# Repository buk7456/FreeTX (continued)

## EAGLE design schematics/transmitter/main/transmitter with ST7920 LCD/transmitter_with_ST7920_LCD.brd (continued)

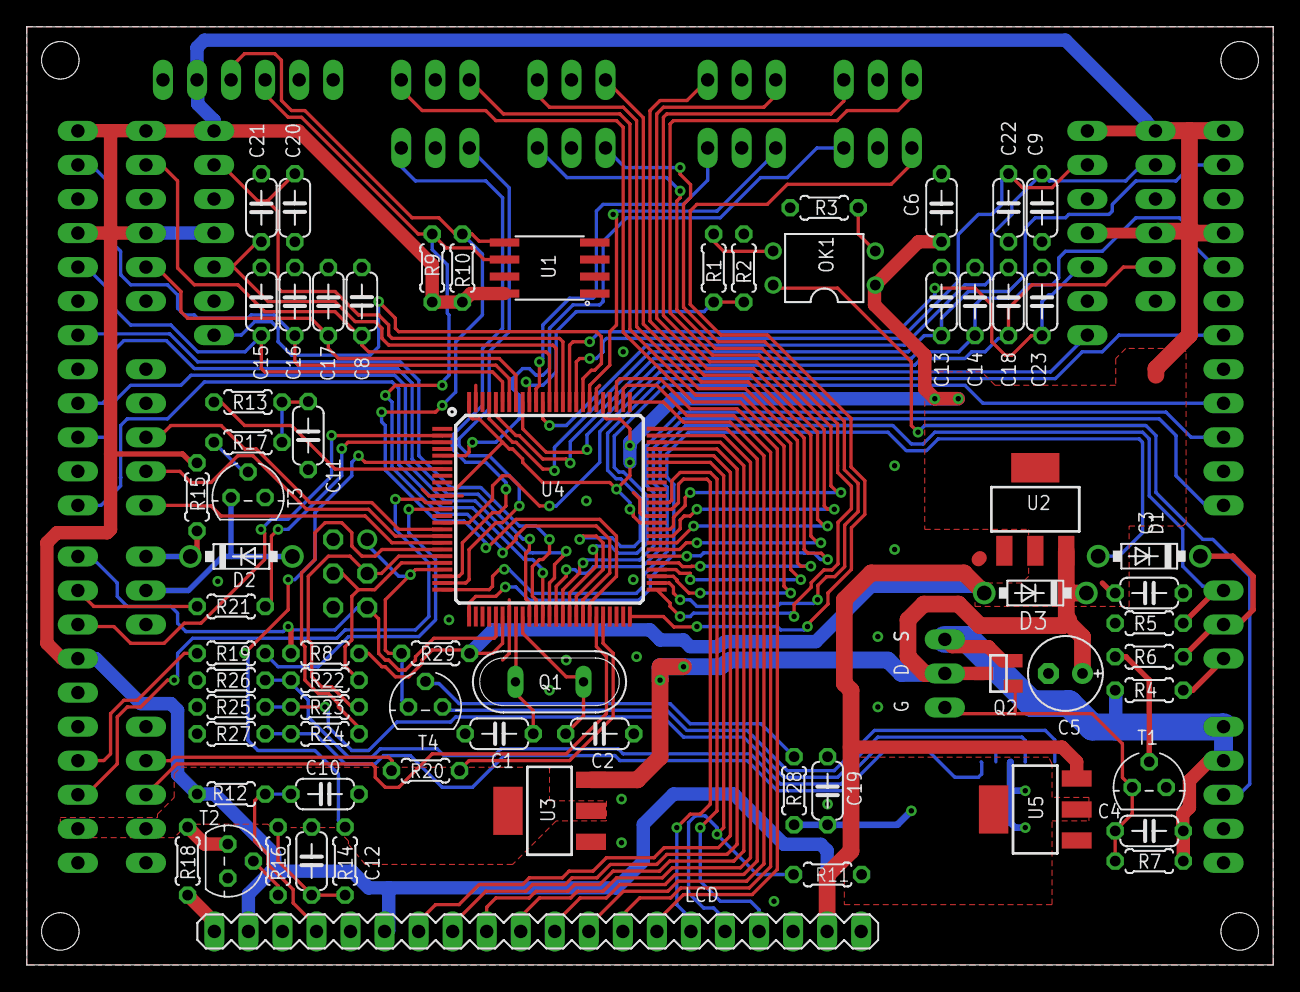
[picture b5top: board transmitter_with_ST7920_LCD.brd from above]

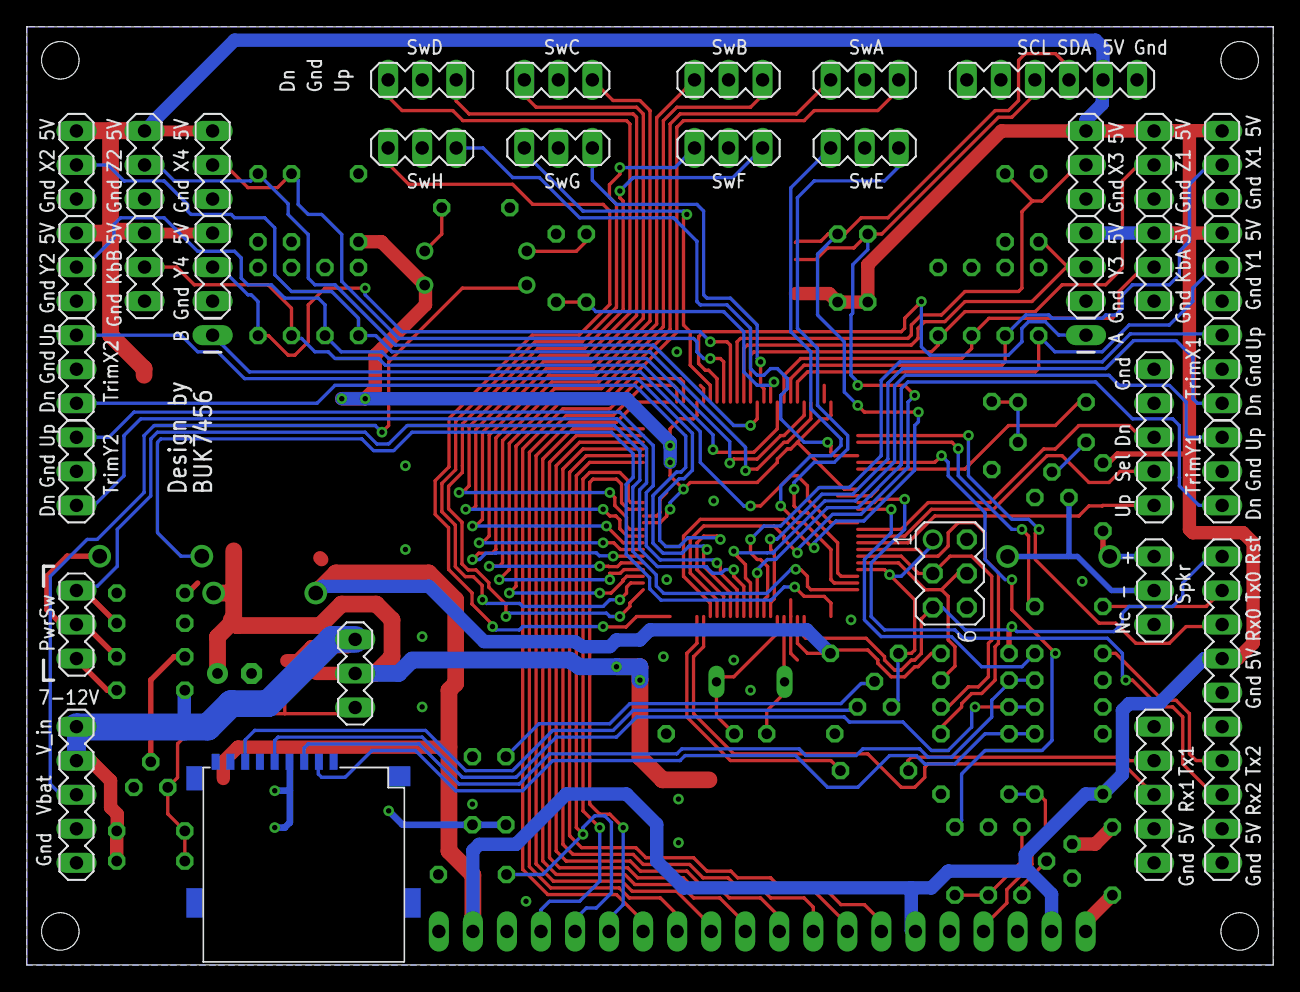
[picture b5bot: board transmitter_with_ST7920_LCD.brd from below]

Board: 2 copper layers, 93.0 x 70.0 mm, 104 parts (37 on the bottom side), 102 nets.

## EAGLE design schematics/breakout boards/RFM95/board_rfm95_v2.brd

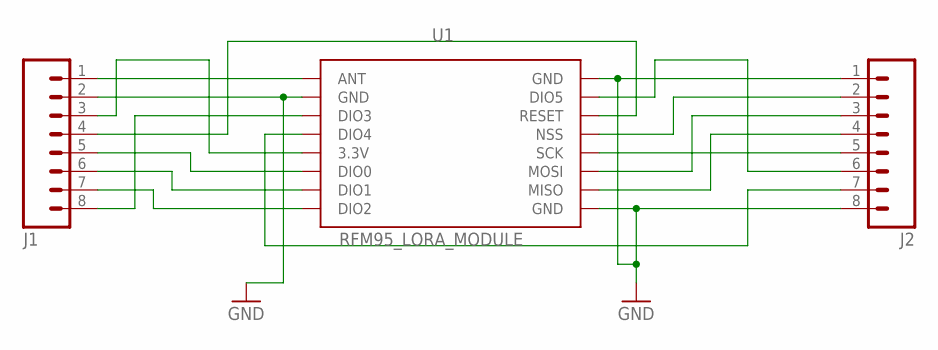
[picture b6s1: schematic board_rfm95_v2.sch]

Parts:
J1, J2: M08; 1X08_ROUND
U1: RFM95_LORA_MODULE; RFM95

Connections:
3.3V: J1.3, U1.3.3V
ANT: J1.1, U1.ANT
DIO0: J1.5, U1.DIO0
DIO1: J1.6, U1.DIO1
DIO2: J1.7, U1.DIO2
DIO4: J2.7, U1.DIO4
DIO5: J2.6, U1.DIO5
GND: J1.2, J2.1, J2.8, U1.GND, U1.GND@1 (GND), U1.GND@2 (GND)
MISO: J2.4, U1.MISO
MOSI: J2.3, U1.MOSI
unnamed: J1.8, U1.DIO3
NSS: J2.2, U1.NSS
RST: J1.4, U1.RESET
SCK: J2.5, U1.SCK

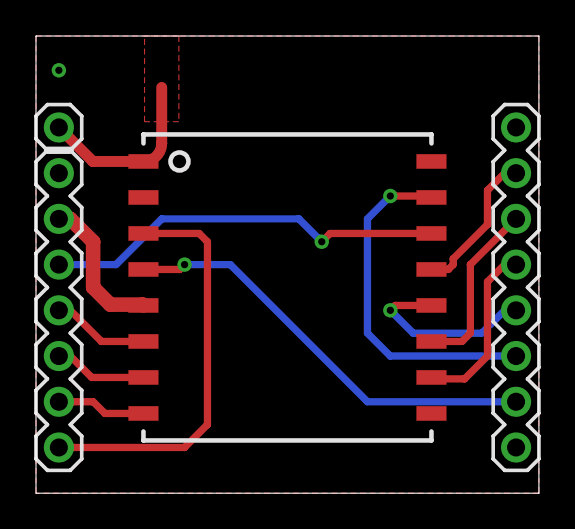
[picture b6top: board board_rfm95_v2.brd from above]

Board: 2 copper layers, 27.9 x 25.4 mm, 3 parts (0 on the bottom side), 14 nets.

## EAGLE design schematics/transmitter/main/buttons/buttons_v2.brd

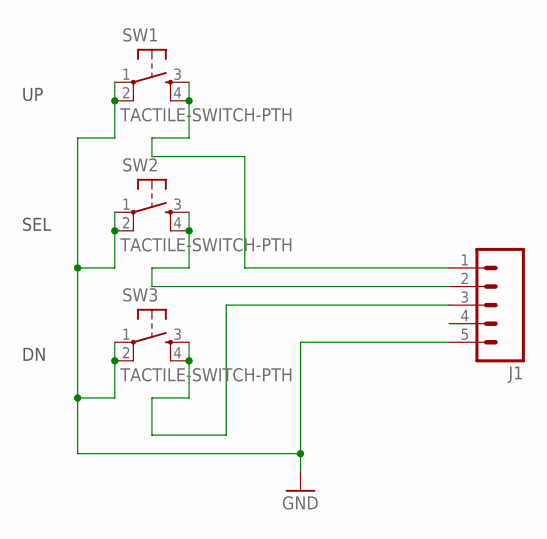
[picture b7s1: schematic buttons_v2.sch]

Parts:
J1: M05PTH; 1X05
SW1, SW2, SW3: TACTILE-SWITCH-PTH; TAC-SWITCH-PTH

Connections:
GND: J1.5, SW1.1, SW1.2, SW2.1, SW2.2, SW3.1, SW3.2
unnamed: J1.1, SW1.3, SW1.4
unnamed: J1.3, SW3.3, SW3.4
unnamed: J1.2, SW2.3, SW2.4

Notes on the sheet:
SEL

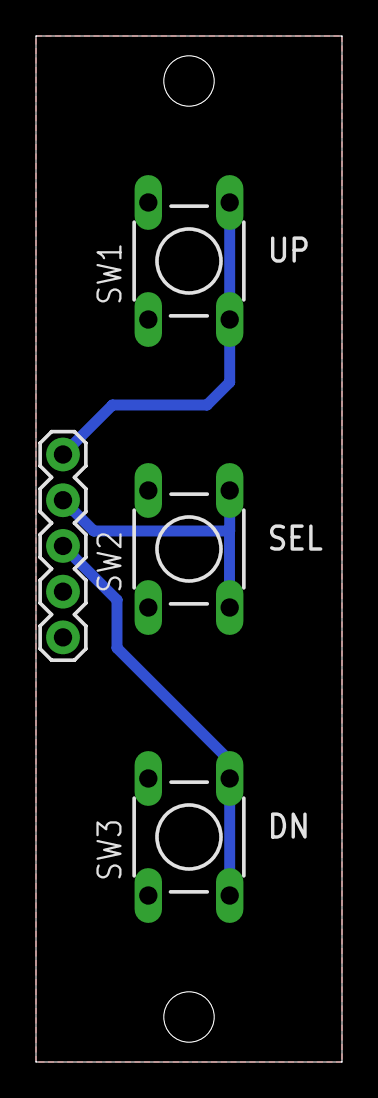
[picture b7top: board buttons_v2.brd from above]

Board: 2 copper layers, 17.0 x 57.0 mm, 4 parts (0 on the bottom side), 4 nets.

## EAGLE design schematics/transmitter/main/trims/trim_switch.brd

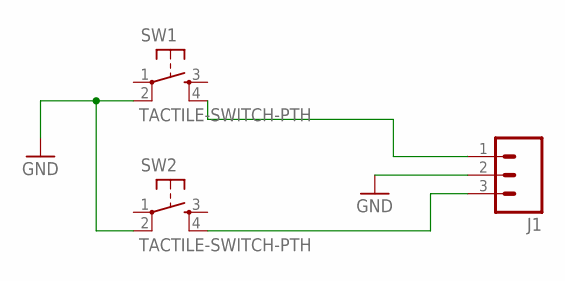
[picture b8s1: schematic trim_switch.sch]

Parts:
J1: M03PTH; 1X03
SW1, SW2: TACTILE-SWITCH-PTH; TAC-SWITCH-PTH

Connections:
GND: J1.2, SW1.2, SW2.2
unnamed: J1.1, SW1.4
unnamed: J1.3, SW2.4

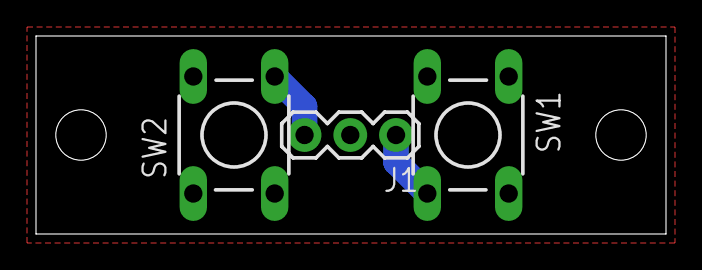
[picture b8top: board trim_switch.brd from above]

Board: 2 copper layers, 35.0 x 11.0 mm, 3 parts (0 on the bottom side), 3 nets.

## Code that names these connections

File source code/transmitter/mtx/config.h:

/*
 * config.h
 *
 * Basic settings such as:
 * - LCD controller
 * - UI to use
 * - Pin mapping
 * - External EEPROM 
 *
 */

#ifndef _CONFIG_H_
#define _CONFIG_H_

#define _FIRMWARE_VERSION "1.5.0"

//===========================================================================
//============================= LCD and UI ==================================
//===========================================================================

#define UI_128X64
// #define UI_84X48  //not implemented

#define DISPLAY_KS0108
// #define DISPLAY_ST7920
// #define DISPLAY_PCD8544 //not implemented

//===========================================================================
//============================= Pins and ports ==============================
//===========================================================================

//Name                 Arduino Pin

#define PIN_X1_AXIS      A3
#define PIN_Y1_AXIS      A2
#define PIN_X2_AXIS      A0
#define PIN_Y2_AXIS      A1
#define PIN_X3_AXIS      A11
#define PIN_Y3_AXIS      A10
#define PIN_X4_AXIS      A13
#define PIN_Y4_AXIS      A12

#define PIN_Z1_AXIS      A9
#define PIN_Z2_AXIS      A8

#define PIN_KNOB_A       A4
#define PIN_KNOB_B       A5

#define PIN_BATTERY_VOLTS    A6

#define PIN_LCD_BACKLIGHT   2
#define PIN_SPEAKER         3

#define PIN_POWER_OFF_SENSE 12
#define PIN_POWER_LATCH     13

#define PIN_KEY_SELECT   8
#define PIN_KEY_UP       9
#define PIN_KEY_DOWN     7

#define PIN_KS_EN        15
#define PIN_KS_RS        14
#define PIN_KS_CS1       4
#define PIN_KS_CS2       39

#define PIN_ST_EN        15
#define PIN_ST_RS        14

//--- Direct port manipulation

#define DDRx_LCD_DATA    DDRA
#define PORTx_LCD_DATA   PORTA

#define DDRx_TRIMS   DDRL
#define PORTx_TRIMS  PORTL
#define PINx_TRIMS   PINL

//--- Physical switches

//Name             Arduino Pin
#define PIN_SWA_UP   37
#define PIN_SWA_DN   36

#define PIN_SWB_UP   35
#define PIN_SWB_DN   34

#define PIN_SWC_UP   33
#define PIN_SWC_DN   32

#define PIN_SWD_UP   31
#define PIN_SWD_DN   30

#define PIN_SWE_UP   10
#define PIN_SWE_DN   11

#define PIN_SWF_UP   41
#define PIN_SWF_DN   40

#define PIN_SWG_UP   61
#define PIN_SWG_DN   69

#define PIN_SWH_UP   5
#define PIN_SWH_DN   38

//--- SD card

#define PIN_SD_CS    53

//===========================================================================
//============================= External EEPROM =============================
//===========================================================================
//Maximum supported is a 512 kbit EEPROM

/* 
//--- 24LC512
//Total bytes (512*1024)/8 => 65536
#define EXTERNAL_EEPROM_TOTAL_BYTES     65536
#define EXTERNAL_EEPROM_PAGE_BYTES      32
#define EXTERNAL_EEPROM_DEVICE_ADDRESS  0x0
 */

//--- 24LC256
//Total bytes (256*1024)/8 => 32768
#define EXTERNAL_EEPROM_TOTAL_BYTES     32768
#define EXTERNAL_EEPROM_PAGE_BYTES      32
#define EXTERNAL_EEPROM_DEVICE_ADDRESS  0x0

#endif

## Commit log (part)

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2025-01-25 Update inputs.cpp
    Improved support for momentary switches.
2025-01-25 Update ui_128x64.cpp
    - Added proper support for momentary switches.
    - Added option to lock menu after inactivity.
    - Turn off inactivity sound without affecting inactivity duration.
    - Show notification settings even when the notification is disabled.
    - Move About screen out of the Advanced menu. Now directly under system settings.
2025-01-25 Update uiCommon.cpp
    - Added proper support for momentary switches.
2025-01-25 Various improvements. (#46)
    * Update common.h
    - Improved support for momentary switches
    * Update common.cpp
    * Update config.h
    * Update stringDefs.cpp
    * Update inputs.cpp
2025-01-25 Update about.h
    - Updated version year.
2025-01-26 Update stringDefs.h
    Added an advanced type of counter.
2025-01-26 Update stringDefs.cpp
    Added an advanced type of counter.
2025-01-26 Update common.h
    Added an advanced counter.
2025-01-26 Update mixer.cpp
    - Added an advanced counter.
    - Counters can now be used inside the mixer.
    - RAM savings.
2025-01-26 Add files via upload
    Update and improve documentation
2025-01-26 Various improvements (#47)
    * Update stringDefs.cpp
    Added an advanced type of counter.
    * Update common.h
    Added an advanced counter.
    * Update common.cpp
    * Update mixer.cpp
2025-01-30 Improved documentation (#48)
    * Delete assets/screens/combined.png
    * Delete doc directory
    * Update README.md
    * Add files via upload
    * Add files via upload
    * Update custom_curves.md
2025-01-30 Update inputs.cpp
    - When playing audio from trim keys, treat them as generic switches if they are disabled for trim adjustments.
2025-01-30 Update ui_128x64.cpp
    - Removed restriction on using trims and flight modes as control switches. They can now be used anywhere.
2025-01-30 Minor improvements (#49)
    * Update inputs.cpp
    - When playing audio from trim keys, treat them as generic switches if they are disabled for trim adjustments.
    * Update uiCommon.h
    * Update uiCommon.cpp
    * Update ui_128x64.cpp
    - Removed restriction on using trims and flight modes as control switches. They can now be used anywhere.
2025-02-04 Update ui_128x64.cpp
    - Show numerical values in mixer output screen when the select key is clicked. Value is shown in form of a tooltip.
2025-02-04 Update ui_128x64.cpp
    - Improve key filtering for backlight on the home screen.
2025-02-05 Add files via upload
    Reorganise doc folder
2025-02-05 Improved documentation (#50)
    * Delete doc directory
    * Add files via upload
    Reorganise doc folder
2025-02-06 Add files via upload
    Fixed various typos.
2025-02-06 Update README.md
    Fixed typos.
2025-02-06 Update config.h
    Bump version number.
2025-02-06 Update mtx.cpp
    - Prevent trim keys from triggering on the backlight when backlight wakeup condition is set to "Keys".
2025-05-17 Update config.h
    Added support for ST7920 based LCD.
2025-05-17 Update font.cpp
    Added support for ST7920 based LCD.
2025-05-17 Update ui_128x64.cpp
    - Added support for ST7920 based LCD.
    - Fixed minor bug in when showing tool-tip in mixer monitor screen, when the output is none.
    - Other minor improvements.
2025-05-17 Update sdStore.cpp
    - Added support for ST7920 LCD.
    - Other minor improvements.
2025-05-17 Update font.h
    Added support for ST7920 LCD.
2025-05-17 Update ui.h
    Added support for ST7920 LCD.
2025-05-17 Add files via upload
    Added support for ST7920 LCD.
2025-05-18 Enhancements: ST7920 LCD Support, Documentation and schematics updates, minor fixes and improvements. (#51)
    * Update readme.md
    * Delete assets/Bm437_Portfolio_6x8_modBUK.FON
    * Add files via upload
    * Update readme.txt
    * Update readme.txt
    * Add files via upload
2025-05-27 Update mixer.md
    Fixed typos.
2025-06-03 Update ui_128x64.cpp
    - Added overview for counter outputs.
2025-06-06 Update ui_128x64.cpp
    Context menus now support horizontal scrolling text for items that won't fit on the screen.
2025-06-06 Update telemetry.md
    Improved the documentation.
2025-06-08 Update ui_128x64.cpp
    - Improved horizontal scrolling behaviour for long text in context menus.
2025-06-14 Update ui_128x64.cpp
    - Minor improvements
2025-07-18 Update tonePlayer.cpp
    Fix typos
2025-07-18 Update config.h
    Fix typos
2025-07-18 Update mtx.cpp
    Fix typos
2025-07-18 Update common.cpp
    Fix typos
2025-07-18 Update common.h
    Fix typos
2025-07-18 Update bitmaps.h
    Fix typos
2025-07-18 Update uiCommon.cpp
    Fix typos
2025-07-18 Update ui_128x64.cpp
    Fix typos
2025-07-18 Update inputs.cpp
    Fix typos
2025-07-18 Update mixer.cpp
    Fix typos
2025-07-18 Update receiver.cpp
    Fix typos
2025-07-18 Fix typos (#52)
    * Update tonePlayer.cpp
    Fix typos
    * Update config.h
    Fix typos
    * Update mtx.cpp
    Fix typos
2025-07-19 Update mixer.md
    Fix typos
2025-07-19 Update logical_switches.md
    - Fix typos
2025-07-28 Minor improvements (#53)
    * Update mtx.cpp
    * Update sdStore.h
    * Update sdStore.cpp
    * Update config.h
    * Update ui_128x64.cpp
    * Update ui.h
2025-07-28 Update ui_128x64.cpp
    - Fix overflowing text in mixer screen when showing curve preview.
2025-08-02 Update stringDefs.cpp
    - Improve consistency in naming
2025-08-02 Update ui_128x64.cpp
    Minor optimizations and improvements.
2025-08-07 Fix typos in comments (#54)
    * Update receiver.cpp
    * Update rfComm.cpp
    * Update rfComm.cpp
    * Update common.h
    * Update inputs.cpp
    * Update mathHelpers.cpp
2025-08-09 Update receiver.cpp
    Fix typos.
2025-08-09 Update rfComm.cpp
    Fix typos.
2025-08-09 Update tonePlayer.cpp
    Fix typos.
2025-08-09 Update config.h
    Fix typos.
2025-08-24 Update modelExport.cpp
    - Remove hard-coded source names.
2025-08-24 Update ui_128x64.cpp
    - Improve character mapping in the text editing dialog.
2025-09-01 Update modelExport.cpp
    Fix typos.
2025-09-01 Update modelImport.cpp
    Fix typos.
2025-09-13 Update mixer.cpp
    - Improved the resolution (samples per cycle and depth) of the generated sine waveform in the function generator.
2025-11-09 Update ui_128x64.cpp
    - Minor improvements; show a space between the value and units in curves screen and debug screen.
2025-11-09 Update config.h
    - Bump version number
2025-11-09 Update modelImport.cpp
    - Improve backward compatibility for model files exported from very old versions.
2025-11-09 Update stringDefs.h
    - Improve backward compatibility for model files exported from very old versions.
2025-11-09 Update stringDefs.cpp
    - Improve backward compatibility for model files exported from very old versions.
2025-11-09 Add files via upload
    Update screenshots
2025-11-09 Minor improvements (#57)
    * Update ui_128x64.cpp
    - Minor improvements; show a space between the value and units in curves screen and debug screen.
    * Update config.h
    - Bump version number
    * Update modelImport.cpp
    - Improve backward compatibility for model files exported from very old versions.
2025-11-27 Update ui_128x64.cpp
    - Added a tooltip in the mixer overview screen that shows additional information about the specific mix. User can access it by clicking the Select key.
    - Moved the mixer curve preview toggle to the mixer context menu, from Miscellaneous settings. This change improves visibility and makes the feature more easily discoverable.
2025-11-27 Minor improvements (#58)
    - Added a tooltip in the mixer overview screen that shows additional information about the specific mix. User can
    access it by clicking the Select key.
    - Moved the mixer curve preview toggle to the mixer context menu, from Miscellaneous settings. This change
    improves visibility and makes the feature more easily discoverable.
2025-12-25 Update ui_128x64.cpp
    - Some memory savings in the UI code.
    - Increased default telemetry sensor slots from 6 to 8.
2025-12-25 Update common.h
    - Some memory savings in the UI code.
    - Increased default telemetry sensor slots from 6 to 8.
2025-12-25 Minor improvements (#60)
    - Some memory savings in the UI code.
    - Increased default telemetry sensor slots from 6 to 8.
    - Added User guide in PDF and ODT formats.
2025-12-26 Update ui_128x64.cpp
    - Some additional memory savings.
2025-12-26 Update stx.ino
    - Fix typos
2025-12-26 Update receiver.ino
    - Fix typos
2025-12-28 Update ui_128x64.cpp
    - Fixed minor issue where resetting the GNSS Altitude AGL or Starting point did not automatically reset
    the corresponding telemetry sensor statistics (maximum and minimum).
2025-12-28 Minor improvements (#61)
    - Fixed minor issue where resetting the GNSS Altitude AGL or Starting point did not automatically reset
    the corresponding telemetry sensor statistics (maximum and minimum).
2026-01-02 Update uiCommon.cpp
    - Fixed minor issue in the UI where we could not select the input source in mixer, etc., if the
    raw source for Rud, Ail, and Ele inputs is set to None.
2026-01-02 Add files via upload
    - Updated documentation.
2026-01-03 Reorganise source code folders
2026-01-03 Reorganise source code folders (#62)
2026-03-25 Added back up and restore for system settings.
2026-03-25 Update documentation
2026-03-25 Minor improvements (#64)
    - Added backup and restore of system settings to/from the SD card.
    - Enabled restoring system settings during initial setup.
    - Disabled key-press sounds by default.
    - Other minor improvements and fixes.
2026-04-18 Update ui_128x64.cpp
    - Fix minor issue of audio getting stuck when backing up or restoring system settings.
2026-05-18 Add files via upload
    Improve documentation
2026-05-18 Update ui_128x64.cpp
    Improved the stick and knob calibration screens.
2026-05-18 Update uiCommon.cpp
    Removed redudant code and variables in the notification handler function.
2026-05-18 Delete doc/User guide.pdf
    Removed outdated user guide.
2026-05-18 Add files via upload
    Update documentation, fix typos.
2026-06-22 Update mtx.cpp
    Minor code refactoring in the controlBacklight() function.
2026-06-26 Improve documentation (#66)
    - Fixed minor issue of blurry SVG image.
2026-06-26 Improve documentation (#67)
2026-06-26 Update config.h
    - Bump version.
